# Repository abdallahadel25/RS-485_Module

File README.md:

# RS-485 Module

A bidirectional RS-485 module that is based on max485 ic

Schematic and PCB are designed using Eagle

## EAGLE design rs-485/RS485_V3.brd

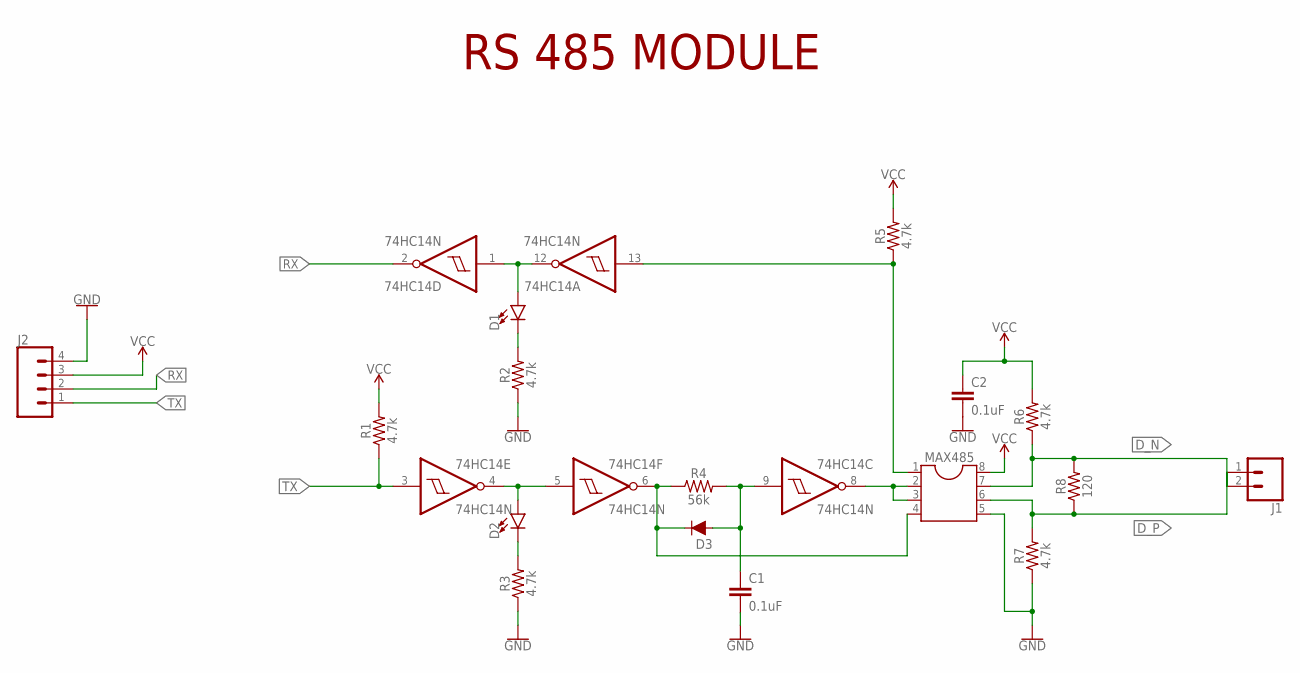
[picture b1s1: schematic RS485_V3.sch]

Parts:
74HC14: 74HC14N; DIL14
C1, C2: 0.1uF; CAP-PTH-SMALL-KIT
D1, D2: LED5MM-KIT; LED_5MM-KIT
D3: 200mA/100V/1V; DIODE-1N4148
J1: CONN_02POLAR; MOLEX-1X2
J2: CONN_04POLAR; MOLEX-1X4
MAX485: DIL8; DIL08
R1, R2, R3, R5, R6, R7: 4.7k; AXIAL-0.3
R4: 56k; AXIAL-0.3
R8: 120; AXIAL-0.3

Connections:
D_N: J1.2, MAX485.7, R6.P$1 (1), R8.P$2 (2)
D_P: J1.1, MAX485.6, R7.P$2 (2), R8.P$1 (1)
GND: 74HC14.7 (GND), C1.2, C2.2, J2.4, MAX485.5, R2.P$1 (1), R3.P$1 (1), R7.P$1 (1)
unnamed: 74HC14.1 (I), 74HC14.12 (O), D1.A
unnamed: D1.K (C), R2.P$2 (2)
unnamed: 74HC14.4 (O), 74HC14.5 (I), D2.A
unnamed: D2.K (C), R3.P$2 (2)
unnamed: 74HC14.9 (I), C1.1, D3.A, R4.P$2 (2)
unnamed: 74HC14.6 (O), D3.C, MAX485.4, R4.P$1 (1)
unnamed: 74HC14.8 (O), MAX485.2, MAX485.3
unnamed: 74HC14.13 (I), MAX485.1, R5.P$1 (1)
RX: 74HC14.2 (O), J2.2
TX: 74HC14.3 (I), J2.1, R1.P$1 (1)
VCC: 74HC14.14 (VCC), C2.1, J2.3, MAX485.8, R1.P$2 (2), R5.P$2 (2), R6.P$2 (2)

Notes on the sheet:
RS 485 MODULE

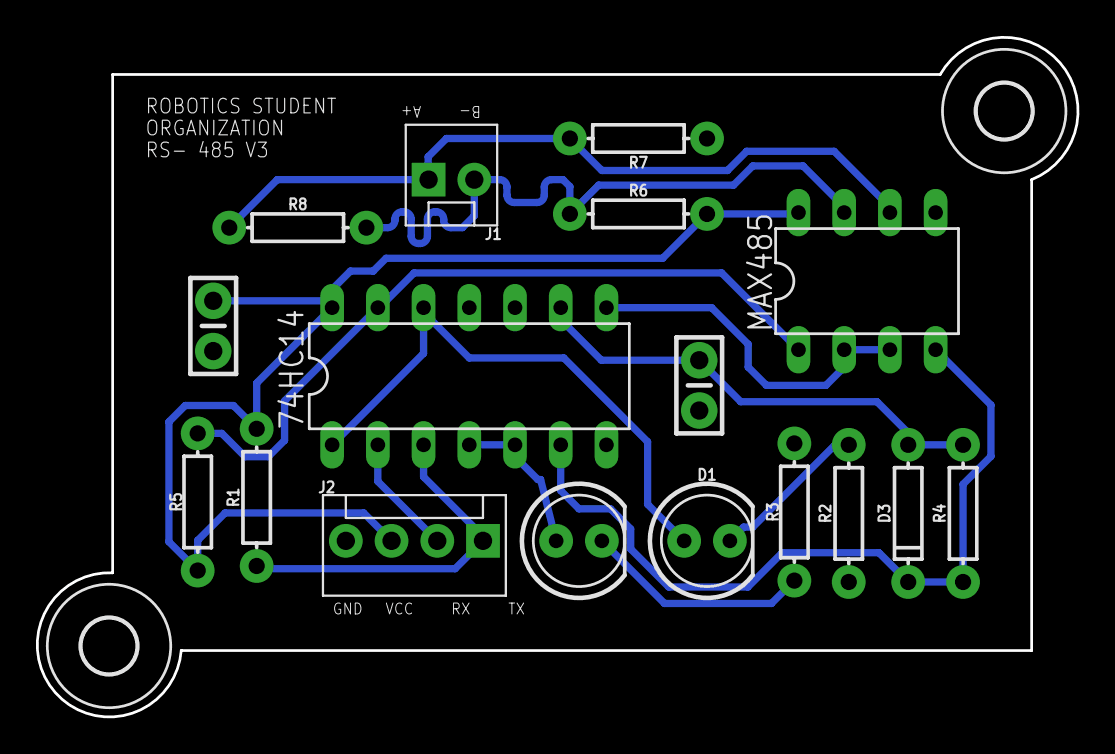
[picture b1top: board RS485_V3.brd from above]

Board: 2 copper layers, 57.8 x 37.7 mm, 19 parts (0 on the bottom side), 14 nets.

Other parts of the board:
U$1, U$2: 3,0

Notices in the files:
parts and their libraries:
SparkFun-Capacitors: Licensing: Creative Commons ShareAlike 4.0 International - https://creativecommons.org/licenses/by-sa/4.0
